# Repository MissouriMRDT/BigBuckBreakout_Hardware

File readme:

here be some discraceful breakout

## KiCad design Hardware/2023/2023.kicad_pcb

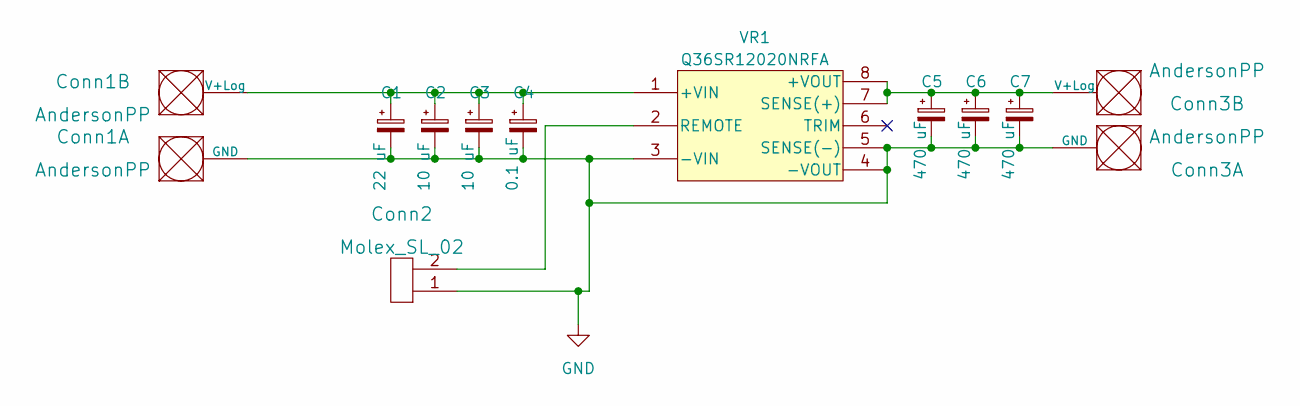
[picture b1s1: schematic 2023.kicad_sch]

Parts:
C1: 22 uF; CP_Radial_D5.0mm_P2.00mm
C2, C3: 10 uF; C_1210_3225Metric_Pad1.33x2.70mm_HandSolder
C4: 0.1 uF; C_1206_3216Metric_Pad1.33x1.80mm_HandSolder
C5, C6, C7: 470 uF; CP_Radial_D8.0mm_P3.50mm
Conn1, Conn3: AndersonPP; Square_Anderson_2_H_Side_By_Side
Conn2: Molex_SL_02; MOLEX_SL_02_Horizontal
VR1: Q36SR12020NRFA

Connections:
GND: C1.2, C2.2, C3.2, C4.2, C5.2, C6.2, C7.2, Conn1.1 (GND), Conn2.1, Conn3.1 (GND), VR1.3 (-VIN), VR1.4 (-VOUT), VR1.5 (SENSE(-))
unnamed: C1.1, C2.1, C3.1, C4.1, Conn1.2 (V+Log), VR1.1 (+VIN)
unnamed: C5.1, C6.1, C7.1, Conn3.2 (V+Log), VR1.7 (SENSE(+)), VR1.8 (+VOUT)
unnamed: Conn2.2, VR1.2 (REMOTE)

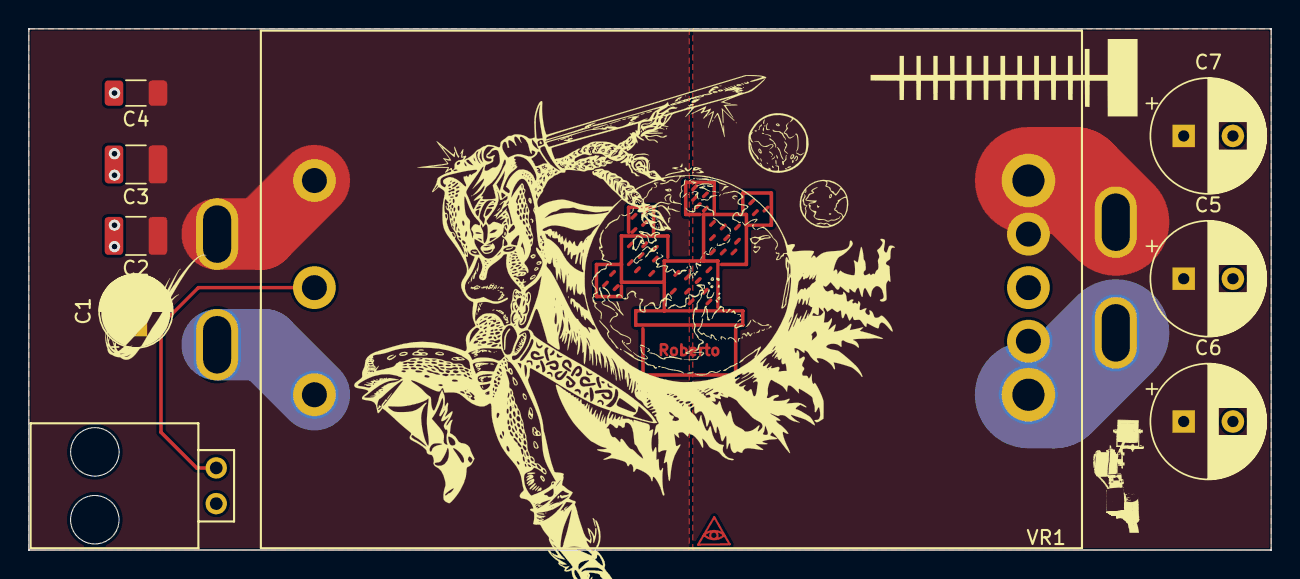
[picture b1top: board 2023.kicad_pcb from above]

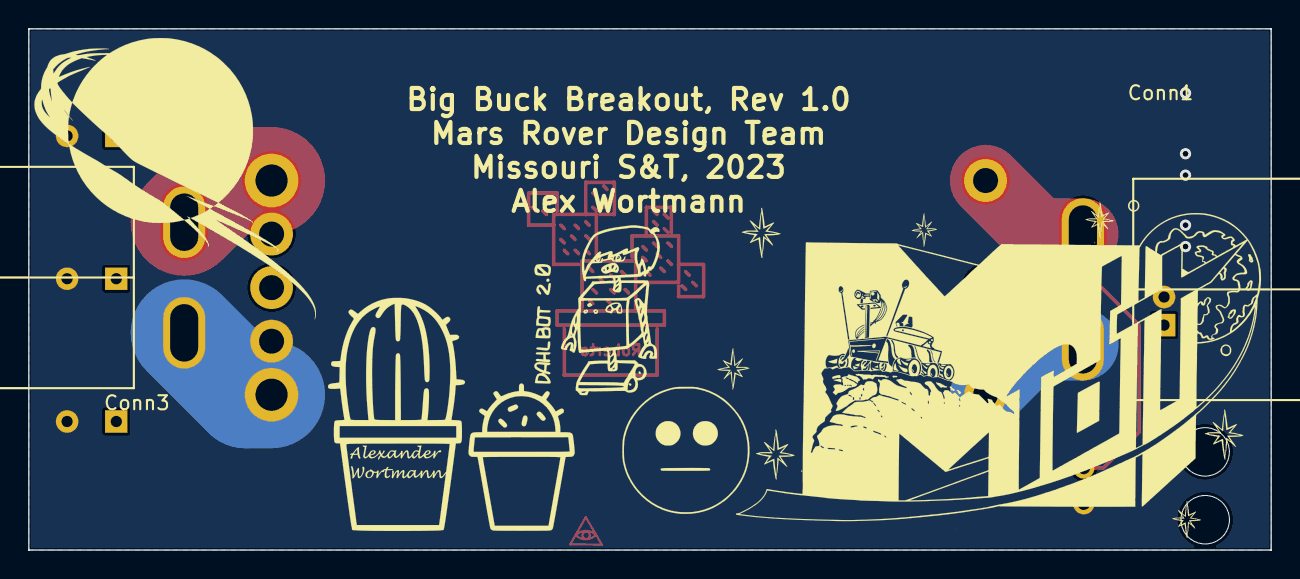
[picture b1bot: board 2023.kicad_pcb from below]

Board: 2 copper layers, 88.4 x 37.1 mm, 11 parts (2 on the bottom side), 4 nets.

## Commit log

2023-03-21 Created breakout
